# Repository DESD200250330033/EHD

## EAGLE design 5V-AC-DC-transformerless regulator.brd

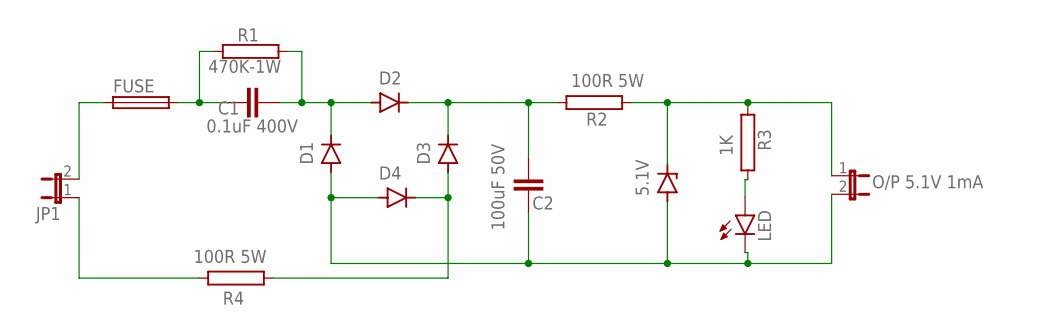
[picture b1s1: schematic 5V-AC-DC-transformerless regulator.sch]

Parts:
C1: 0.1uF 400V; C2.5-3
C2: 100uF 50V; C2.5-3
D1, D2, D3, D4: 1N4004; DO41-10
FUSE: GSH15
JP1: JP1E; JP1
LED: LED; SMARTLED-TTW
O/P: O/P 5.1V 1mA; JP1
R1: 470K-1W; AC01
R2, R4: 100R 5W; AC01
R3: 1K; AC01
ZENER: 5.1V; DO35Z10

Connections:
unnamed: FUSE.1, JP1.2
unnamed: C1.1, FUSE.2, R1.1
unnamed: C1.2, D1.C, D2.A, R1.2
unnamed: LED.A@1 (A), R3.1
unnamed: D3.A, D4.C, R4.2
unnamed: C2.2, D1.A, D4.A, LED.C@1 (C), O/P.2, ZENER.A
unnamed: C2.1, D2.C, D3.C, R2.2
unnamed: O/P.1, R2.1, R3.2, ZENER.C
unnamed: JP1.1, R4.1

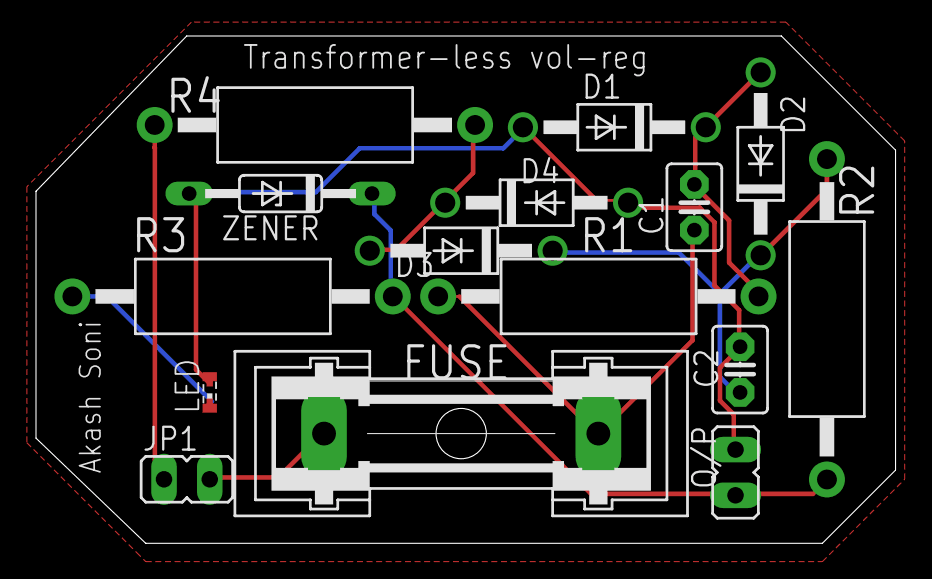
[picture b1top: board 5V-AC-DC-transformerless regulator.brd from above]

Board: 2 copper layers, 47.8 x 28.2 mm, 15 parts (0 on the bottom side), 9 nets.

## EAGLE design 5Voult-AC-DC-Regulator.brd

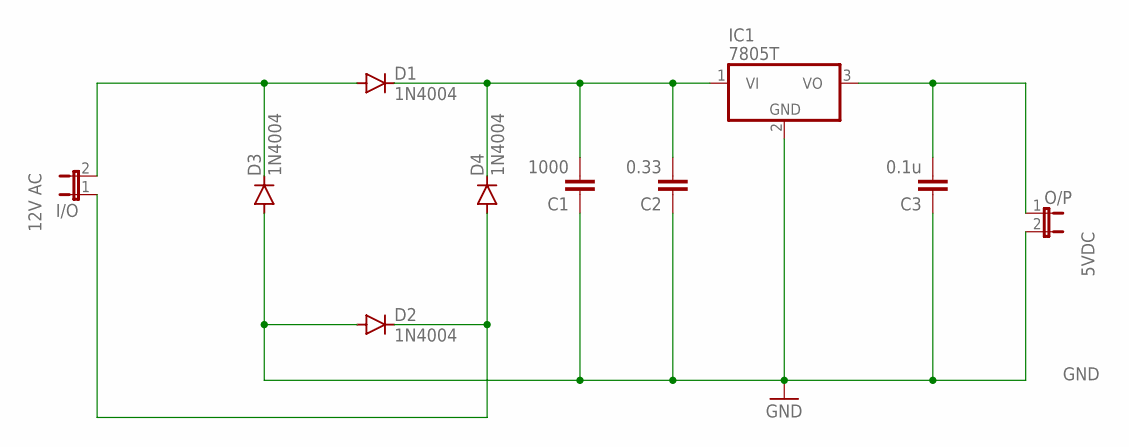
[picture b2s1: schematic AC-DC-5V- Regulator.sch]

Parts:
C1: 1000; C2.5-3
C2: 0.33; C2.5-3
C3: 0.1u; C2.5-3
D1, D2, D3, D4: 1N4004; DO41-10
I/O: JP1E; JP1
IC1: 7805T; TO220H
O/P: JP1E; JP1

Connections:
GND: C1.1, C2.1, C3.1, D2.A, D3.A, IC1.2 (GND), O/P.2
unnamed: D1.A, D3.C, I/O.2
unnamed: D2.C, D4.A, I/O.1
unnamed: C1.2, C2.2, D1.C, D4.C, IC1.1 (VI)
unnamed: C3.2, IC1.3 (VO), O/P.1

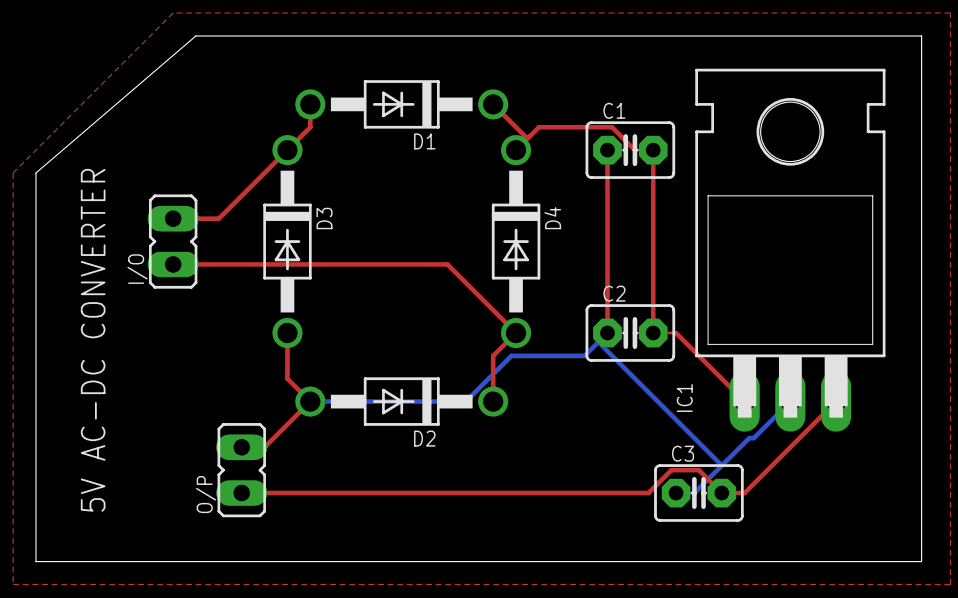
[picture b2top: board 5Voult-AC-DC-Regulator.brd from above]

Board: 2 copper layers, 49.2 x 29.2 mm, 10 parts (0 on the bottom side), 5 nets.

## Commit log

2020-10-06 EHD DESIGN
    EHD DESIGN ASSIGNMENT
